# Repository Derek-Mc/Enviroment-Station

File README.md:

# Enviroment-Station
Keystone project from college (2017).

The objective of the project was to create an enviromantal monitoring station that would measure the humidity, light levels,
temperature, and soil moisture content of a plant.  This data is then sent to a server where the data is the pulled from and
displayed on an Android app and a website.

All files were made by myself with the exception of; Plant1.php, Plant_One_Hum.php, Plant_One_Light.php, Plant_One_Moist.php,
and Plant_One_Temp.php, which were created by my partner on the project.

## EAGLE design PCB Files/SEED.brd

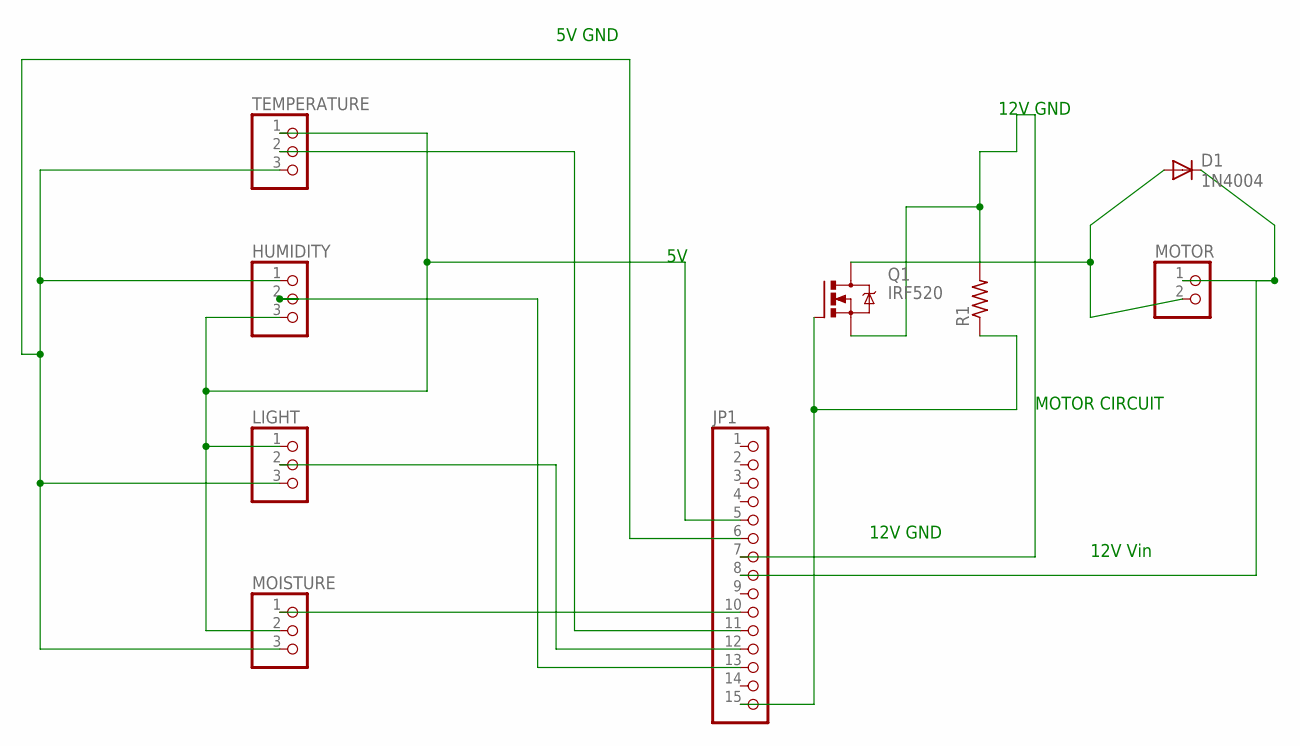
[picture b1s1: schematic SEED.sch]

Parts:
D1: 1N4004; DO41-10
HUMIDITY: PINHD-1X3; 1X03
JP1: PINHD-1X15; 1X15
LIGHT: PINHD-1X3; 1X03
MOISTURE: PINHD-1X3; 1X03
MOTOR: PINHD-1X2; 1X02
Q1: IRF520; TO220BV
R1: R-US_0207/12; 0207/12
TEMPERATURE: PINHD-1X3; 1X03

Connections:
unnamed: JP1.10, MOISTURE.1
unnamed: JP1.11, TEMPERATURE.2
unnamed: JP1.12, LIGHT.2
unnamed: HUMIDITY.2, JP1.13
unnamed: JP1.15, Q1.G, R1.1
unnamed: D1.A, MOTOR.2, Q1.D
unnamed: HUMIDITY.3, JP1.5, LIGHT.1, MOISTURE.2, TEMPERATURE.1
unnamed: D1.C, JP1.8, MOTOR.1
unnamed: JP1.7, Q1.S, R1.2
unnamed: HUMIDITY.1, JP1.6, LIGHT.3, MOISTURE.3, TEMPERATURE.3

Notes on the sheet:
MOTOR CIRCUIT
12V Vin
12V GND
5V GND

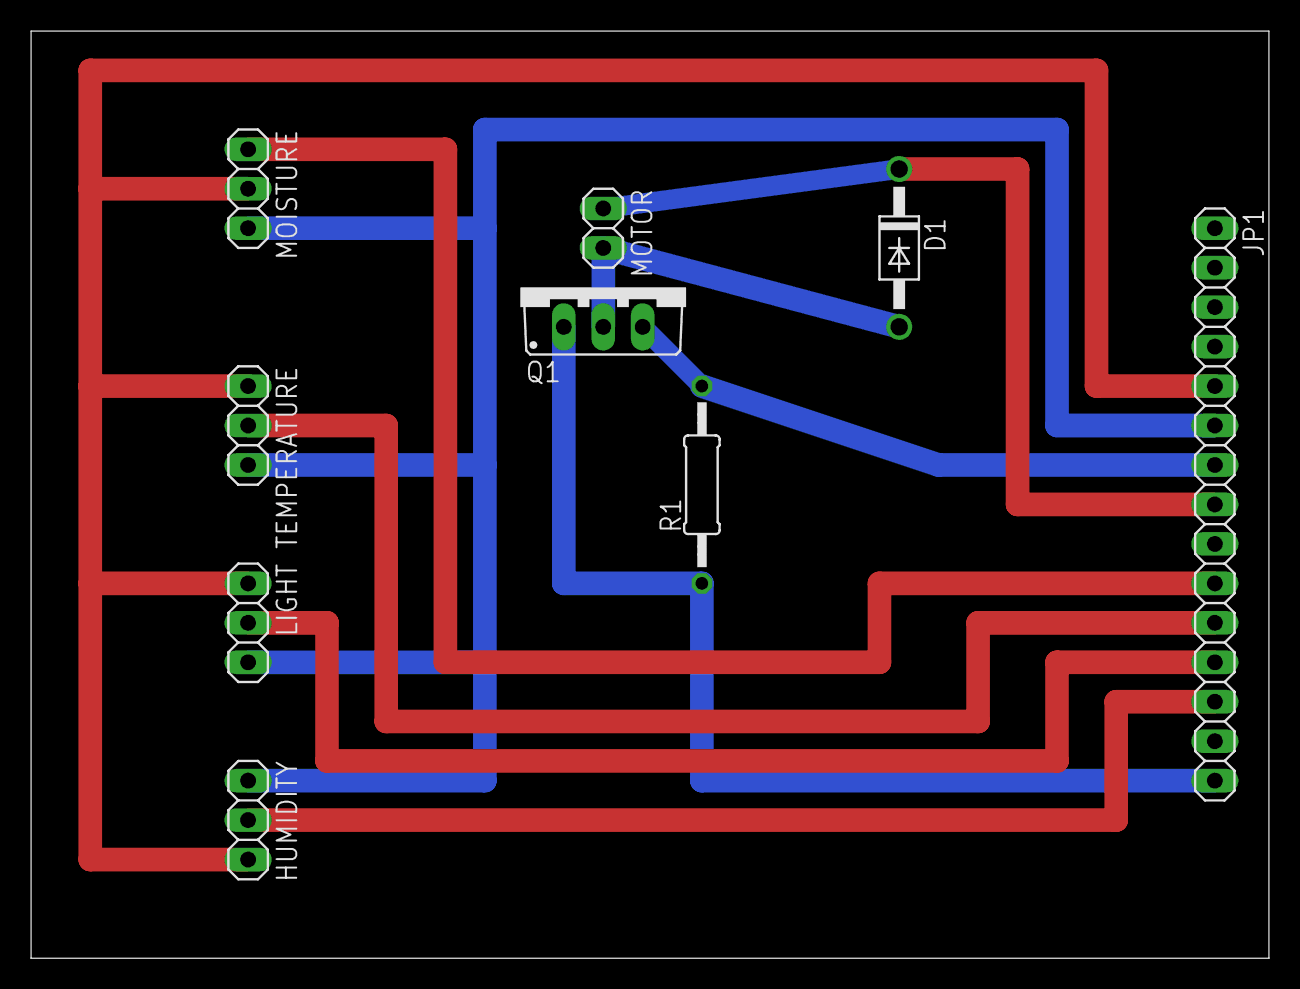
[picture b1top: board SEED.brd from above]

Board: 2 copper layers, 79.7 x 59.7 mm, 9 parts (0 on the bottom side), 10 nets.

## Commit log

2017-05-05 Initial Upload
    Partial test to see if I'm doing things correctly and if I am, then
    uploading my keystone project as it was upon completion of the project.
2017-05-05 Update README.md
    Added additional information.
